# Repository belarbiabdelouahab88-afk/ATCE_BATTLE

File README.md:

# ATCE_BATTLE
L3 SPI EA projet ATCE avec jmf

un groupe de 5 étudiants en licence EEA à l'université UMLP travaillent sur le projet d'ATCE, le but est de concevoir une carte comprenant un microcontrôleur Atmega32U4 chargé d’asservir la fréquence du quartz qui le cadence sur un signal stable fourni par un récepteur GPS.
Ce depot contient tous les fichiers de la partie programmation du microcontroleur.

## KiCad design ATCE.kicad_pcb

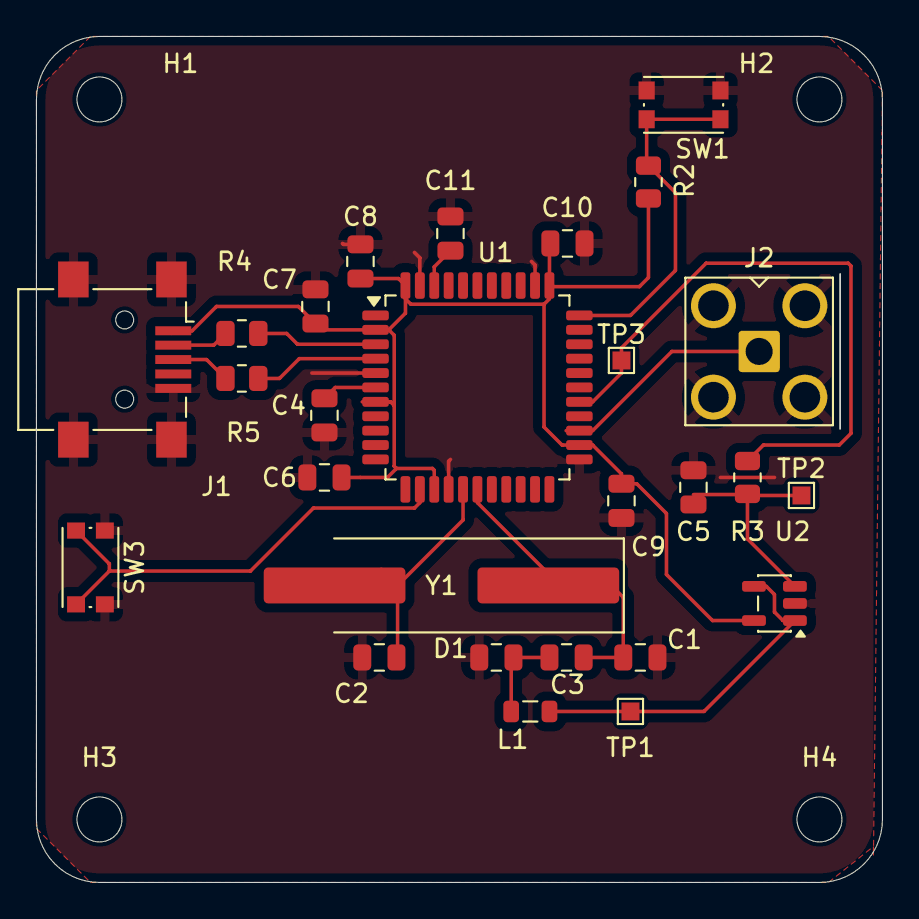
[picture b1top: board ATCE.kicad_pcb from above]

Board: 2 copper layers, 47.0 x 47.0 mm, 31 parts (0 on the bottom side), 17 nets.

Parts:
C1, C2: 20p; C_0805_2012Metric
C3: 5n; C_0805_2012Metric
C4, C11: 1u; C_0805_2012Metric
C5: 10u; C_0805_2012Metric
C6, C7, C8, C9, C10: 100n; C_0805_2012Metric
D1: 1u; C_0805_2012Metric
H1, H2, H3, H4: MountingHole; MountingHole_2.5mm
J1: USB_B_Mini; USB_Mini-B_Lumberg_2486_01_Horizontal
J2: Conn_Coaxial; SMA_Amphenol_901-143_Horizontal
L1: 10u; L_0805_2012Metric
R2, R3: 5.6k; R_0805_2012Metric
R4, R5: 22; R_0805_2012Metric
SW1, SW3: SW_Push; SW_Push_1P1T_NO_CK_KMR2
TP1, TP2, TP3: TestPoint; TestPoint_Pad_1.0x1.0mm
U1: ATmega32U4-A; TQFP-44_10x10mm_P0.8mm
U2: AD8603; TSOT-23-5
Y1: 16M; Crystal_SMD_HC49-SD_HandSoldering

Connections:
+5V: C6.1, C7.1, C8.1, C9.1, C10.1, J1.1 (VBUS), R2.1, U1.2 (UVCC), U1.7 (VBUS), U1.14 (VCC), U1.24 (AVCC), U1.34 (VCC), U1.44 (AVCC), U2.5 (V+)
GND: C1.2, C2.2, C4.2, C5.2, C6.2, C7.2, C8.2, C9.2, C10.2, C11.1, D1.2 (A), J1.5 (GND), J1.6 (Shield), J2.2 (Ext), SW1.2, SW3.1, U1.5 (UGND), U1.15 (GND), U1.23 (GND), U1.35 (GND), U1.43 (GND), U2.2 (V-)
unnamed: C3.1, D1.1 (K), L1.2
unnamed: J1.3 (D+), R4.2
unnamed: J1.2 (D-), R5.2
unnamed: J2.1 (In), U1.25 (PD4)
unnamed: C11.2, U1.42 (AREF)
unnamed: R4.1, U1.4 (D+)
unnamed: R5.1, U1.3 (D-)
unnamed: R3.2, TP3.1, U1.27 (PD7)
unnamed: C4.1, U1.6 (UCAP)
unnamed: C1.1, C3.2, U1.17 (XTAL1), Y1.1
unnamed: C2.1, U1.16 (XTAL2), Y1.2
unnamed: R2.2, SW1.1, U1.33 (~HWB/PE2)
unnamed: SW3.2, U1.13 (~RESET)
unnamed: C5.1, R3.1, TP2.1, U2.3 (+)
unnamed: L1.1, TP1.1, U2.1, U2.4 (-)

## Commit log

2026-02-09 Add files via upload
    1st draft for main schematic
2026-03-23 Create makefile
2026-03-23 Rename ATCE.kicad_pcb to KICAD/ATCE.kicad_pcb
2026-03-23 Rename ATCE.kicad_prl to KICAD/ATCE.kicad_prl
2026-03-23 Rename ATCE.kicad_pro to KICAD/ATCE.kicad_pro
2026-03-23 Rename ATCE.kicad_sch to KICAD/ATCE.kicad_sch
2026-03-24 Update makefile
2026-03-24 Add files via upload
    BOM bill of materials
2026-03-24 Add files via upload
    Partie LED
2026-03-24 Create led.c
    L'allumage des LED et la désactivition du JTAG
2026-03-26 Create pwm
2026-03-27 Create octave code, calcule des coefs pid
2026-03-27 Create pid.c
    Regulation pid (ilya encore des trucs a supprimer)
2026-03-28 PI code
2026-03-28 Rename led.c to led.c
2026-03-28 Rename makefile to makefile
2026-03-28 Update fastpwm.c
    Generation d'une PWM_fast_mode sur le portD7 de l'atmega32u4
2026-03-28 Create Reponse_indicielle.c
    Temps de reponse du systeme a atteindre la consigne
2026-03-28 Rename Reponse_indicielle.c to Reponse_indicielle/Reponse_indicielle.c
2026-03-28 Create point_de_fonct.c
    Variation du rapport cyclique de 0 a 100% sur les mesures de frequences
2026-03-28 Create InputCap.c
    Capture du signal 1PPS sur le compteur du Timer1
2026-03-28 Create mesure_input_capture.txt
    Mesure de l'input capture avec le comportement en frequence lorsque le quartz est soumis a une source chaude dans notre cas c'est le fer a soude
2026-03-28 Add files via upload
    Simulation d'un signal 1PPS avec comme caracteristique une amplitude de 3,3V et un rapport cyclique de 20%
2026-03-28 Add files via upload
    Signal de la PWM en mode Fast avec une frequence de 15Khz
2026-03-28 Add files via upload
    Signal de commande de la regulation PI
2026-03-28 Rename Point de fonctionnement/Point_de_fonctionnement.png to Point de fonctionnement/Graphe/Point_de_fonctionnement.png
2026-03-28 Rename Point de fonctionnement/point_de_fonct.c to Point de fonctionnement/Code/point_de_fonct.c
2026-03-28 Rename Point de fonctionnement/makefile to Point de fonctionnement/Code/makefile
2026-03-28 Rename INPUT capture/InputCap.c to INPUT capture/Code/InputCap.c
2026-03-28 Rename INPUT capture/makefile to INPUT capture/Code/makefile
2026-03-28 Rename INPUT capture/1pps.PNG to INPUT capture/Graphe/1pps.PNG
2026-03-28 Rename INPUT capture/mesure_inputCap.png to INPUT capture/Graphe/mesure_inputCap.png
2026-03-28 Rename INPUT capture/mesure_input_capture.txt to INPUT capture/Graphe/mesure_input_capture.txt
2026-03-28 Rename Reponse_indicielle/Reponse_indicielle.c to Reponse_indicielle/Code/Reponse_indicielle.c
2026-03-28 Rename Reponse_indicielle/makefile to Reponse_indicielle/Code/makefile
2026-03-28 Rename pmw/fastpwm.c to pmw/Code/fastpwm.c
2026-03-28 Rename pmw/makefile to pmw/Code/makefile
2026-03-28 Rename pmw/PWM_fast_mode.PNG to pmw/Graphe/PWM_fast_mode.PNG
2026-03-28 Create Graphe
2026-03-28 Rename PI regulation/PI.c to PI regulation/Code/PI.c
2026-03-28 Rename PI regulation/makefile to PI regulation/Code/makefile
2026-03-28 Rename PI regulation/Commande_PI.png to PI regulation/Graphe/Commande_PI.png
2026-03-28 Rename PI regulation/frequence_PI.png to PI regulation/Code/frequence_PI.png
2026-03-28 Rename frequence_PI.png to frequence_PI.png
2026-03-29 Rename report.txt to Kicad/report.txt
2026-03-29 Rename ${ATCE}.csv to Kicad/${ATCE}.csv
2026-03-29 Rename ATCE.csv to Kicad/ATCE.csv
2026-03-29 Rename ATCEsimulation.kicad_sch to Kicad/ATCEsimulation.kicad_sch
2026-03-29 Rename ATCEsimulation.wbk to Kicad/ATCEsimulation.wbk
2026-03-29 Rename ATCEsimulation_PWM.kicad_sch to Kicad/ATCEsimulation_PWM.kicad_sch
2026-03-29 Rename ATCEsimulation_PWM.wbk to Kicad/ATCEsimulation_PWM.wbk
2026-03-29 Rename ATCEsimulation_Resonateur.kicad_sch to Kicad/ATCEsimulation_Resonateur.kicad_sch
2026-03-29 Rename ATCEsimulation_Resonateur.wbk to Kicad/ATCEsimulation_Resonateur.wbk
2026-03-29 Rename fp-info-cache to Kicad/fp-info-cache
2026-03-29 Rename opampsim.lib.txt to Kicad/opampsim.lib.txt
